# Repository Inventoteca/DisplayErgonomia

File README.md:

# DisplayErgonomia
Display que muestra diferentes valores del entorno. Usa NeoDígitos y varios sensores.  

+ Una Raspberry Pi Zero W controla los Neodígitos y recibe información de los sensores  
+ Almacena los valores que se podrían mostrar en forma de gráficas  
+ Los sensores de luz se instalan en la parte de arriba, cubiertos con una ventana de acrílico  
+ Caja para proteger raspberry y conexiones  
+ "Espiroqueta" para agrupar los cables  
+ Clema molex en los grupos de NeoDígitos para facilitar las conexiones  
+ NeoDígitos atornillados a base de MDF  
+ Raspberry con shield  

## Dígitos
Ocupa 17 NeoDígitos medianos que tienen 2 Neopixels por segmento más 2 Neopixels separados  
Son 16 Neopixels por dígito. En total son 272 Neopixels en el display  

La guía de Adafruit recomienda considerar que cada Neopixel consume 20 mA  
20 mA * 272 = 5.44 A
La Raspberry Zero W puede consumir 2 A  
5.44 A + 2 A = 7.44 A
Una fuente de 10 A es la elegida  

Cada Neopixel consume alrededor de 60 mA con brillo al máximo. 60 mA * 272 = 16.32 A  
Es muy raro que se lleguen a prender con el brillo máximo    
https://learn.adafruit.com/adafruit-neopixel-uberguide/individual-neopixels  

## Sensores

### ADC
Opciones de Convertidores Analógico a Digital  

MCP3008 - 8 channels of analog input with 10-bit precision  
ADS1x15 series - 4 channels with 12 to 16-bit precision and a programmable gain stage  
PCF8591 - 4 canales ADC, 1 canal DAC, resolución 8 bits, interfaz I2C  

https://learn.adafruit.com/raspberry-pi-analog-to-digital-converters  
https://articulo.mercadolibre.com.mx/MLM-544163593-modulo-analogico-digital-3-adc-1-dac-pcf8591-arduino-pic-dsp-_JM  

Se usa el **ADS1115** que tiene resolución de 16 bits.  

Datasheet  
https://www.ti.com/lit/ds/symlink/ads1113.pdf?ts=1616968419755  

Producto de Adafruit  
https://www.adafruit.com/product/1085  
https://github.com/adafruit/Adafruit_ADS1X15  

Tutorial para usar con Arduino  
https://www.luisllamas.es/entrada-analogica-adc-de-16-bits-con-arduino-y-ads1115/  

### Índice UV

Encontramos dos opciones para medir la radiación UV: Si1145 y ML8511.  
Se eligió el ML8511 porque la salida es voltaje analógico (no se requiere una librería específica para el sensor)
y tiene un fotodiodo sensible a la luz UV, en cambio el Si1145 no mide la luz UV directamente, la calcula
a partir de la luz visible e infrarroja.  

ML8511  
https://cdn.sparkfun.com/datasheets/Sensors/LightImaging/ML8511_3-8-13.pdf  
The ML8511 is a UV sensor, which is suitable for acquiring UV intensity indoors or outdoors. The ML8511 is
equipped with an internal amplifier, which converts photo-current to voltage depending on the UV intensity.
This unique feature offers an easy interface to external circuits such as ADC.  
Photodiode sensitive to UV-A and UV-B  
Analog voltage output  
Operating Voltage 3.3 V  
Output Voltage 1.0 - 3.0 V (depende de temperatura)  
Se debe conectar ADC a la salida  
280 a 390nm  

Si1145  
https://learn.adafruit.com/adafruit-si1145-breakout-board-uv-ir-visible-sensor  
https://github.com/adafruit/Adafruit-Si1145-Light-Sensor-PCB  
https://cdn-shop.adafruit.com/datasheets/Si1145-46-47.pdf  
The SI1145 (from SiLabs) has a calibrated UV sensing algorithm that can calculate UV Index.
It doesn't contain an actual UV sensing element, instead it approximates it based on visible & IR light from the sun.
Works over I2C so just about any microcontroller can use it.
Has individual visible and IR sensing elements, but the library doesn't calculate the exact values of IR and Visible light.
If you need precision Lux measurement check out the TSL2561.

### Sonido
Probaremos con el módulo KY-037 tomando muestras con el ADS1115.  

Tutorial para usar con Arduino  
https://create.arduino.cc/projecthub/electropeak/how-to-use-ky-037-sound-detection-sensor-with-arduino-a757a7  

Otras opciones para medir sonido se muestran abajo. No se han probado.  

Hat con micrófono  
https://medium.com/homeday/building-a-noise-level-dashboard-for-your-office-with-a-raspberry-pi-71360ee1ff46  
https://thepihut.com/products/respeaker-4-mic-array-for-raspberry-pi  

¿Usar la entrada de micrófono o un micrófono USB?  
https://www.raspberrypi.org/forums/viewtopic.php?t=258965  

Diseño de una herramienta de medición de ruidos (con módulo micrófono DfRobot 0034)  
http://www.scielo.org.co/pdf/pml/v12n1/1909-0455-pml-12-01-00081.pdf  

### Luz (emitancia luminosa)  
Se mide en lux  
https://es.wikipedia.org/wiki/Emitancia_luminosa  

El sensor elegido es el **TSL2561**. Es fácil de usar con las librerías.  
El valor en el display se podría mostrar en kilolux, de ese modo se puede mostrar todo el rango
de medición del sensor 0.001 hasta 40.00 kilolux.  

Tutoriales (Arduino)  
https://learn.adafruit.com/tsl2561/overview  
https://hetpro-store.com/TUTORIALES/sensor-de-luz-tsl2560/  

Datasheet  
https://ams.com/TSL2561#tab/documents  

### Calidad del aire
El sensor MQ-135 se utiliza en equipos de control de calidad del aire para edificios y oficinas,
son adecuados para la detección de NH3, NOx, alcohol, benceno, humo, CO2, etc.  
Se debe calibrar.  

Tutoriales para empezar con Arduino  
https://naylampmechatronics.com/blog/42_tutorial-sensores-de-gas-mq2-mq3-mq7-y-mq135.html  
https://www.luisllamas.es/arduino-detector-gas-mq/  

Datasheet  
http://www.china-total.com/Product/meter/gas-sensor/MQ135.pdf  
http://www.china-total.com/Product/meter/gas-sensor/Gas-sensor.htm  

Librería para sensores MQ  
Podemos basarnos en las funciones de regresión  
https://github.com/miguel5612/MQSensorsLib  

## Raspberry
Los sensores serán leidos por la Raspberry y sus valores serán mostrados por los NeoDígitos, el programa funciona con Node-RED, con 
los módulos necesarios y librerias contenidas en una imagen de Docker. El control de los Dígitos está realizado por un nodo desarrollado 
por nosotros. Otro contenedor de Docker administrará el WiFi, para ser el medio de configuración del panel, através de un Dashboard.

Wifi  
Es necesario configurar la Raspberry como AP + Client al mismo tiempo, se realizó con las instrucciones siguientes, basadas en este tutorial.  
https://pifi.imti.co/  

- Con la Raspberry corriendo ya algún S.O. y conectada a Internet por cable, con SSH activado, 
se procede a desconecatar el wifi del sistema y se le pasa el control a un contenedor de Docker.
- Se ha probado con RPi Zero W, RPi 3. Se debe terminar la configuración de país del wifi antes de proceder a quitarlo del sistema.

## Diagramas
Dibujos de conexiones se encuentran en la carpeta `Diagramas`.

## Diseños
La carpeta `Diseños` contiene 

+ El modelo 3D del display
+ Piezas en STL para imprimir
+ Los dibujos para cortar las piezas de MDF
+ PCBs en formato Eagle

## Documentos
En la carpeta `Documentos` está la hoja de cotización y otra información privada.

## Fotos
En la carpeta `Fotos` hay imágenes del proceso de ensamblaje.

## Programa
La carpeta `Programa` contiene 

+ Descripciones de las librerías
+ Comandos utilizados para instalar las librerías
+ Capturas de pantalla

Se ha creado un repositorio independiente para sincronizar los programas desde Node-RED.
Contiene los flujos de Node-RED y programas escritos en python.  
https://github.com/Inventoteca/DisplayErgonomiaFlows

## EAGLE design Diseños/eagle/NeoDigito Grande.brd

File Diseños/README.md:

En esta carpeta se encuentran los diseños las piezas para armar el
Display Ergonomía.

En primer lugar está el ensamblaje completo en formato step.

En la carpeta `corte_laser` se tienen los dibujos para cortar mdf de 3 mm y 6 mm. 
El archivo `Panel ergonomia corte.dwg` es el primer diseño que enviaron para 
cortar el panel frontal. Se redibujó y se agregaron los puntos decimales de 
los dígitos y perforaciones para las pijas.  

En la carpeta `eagle` se tienen estos diseños
- Tres tamaños de NeoDigitos
- Shield para Raspberry Pi Zero
- Placas para los sensores
- Placas para las borneras

En el display se utilizan los NeoDigitos medianos V2 y el shield para Rasp.

La carpeta `stl` contiene modelos para fabricar con impresión 3D. Son cajas
para los sensores y separadores para las placas de las borneras.

----

## Modelos 3D descargados  

Caja 25 x 15 x 10 cm  
https://grabcad.com/library/lemotech-ip67-junction-box-250-mm-x-150-mm-x-100-mm-1  

Otras cajas (no descargadas)  
https://grabcad.com/library/ip65-ip67-electrical-enclosures-2/details?folder_id=4320709  

Power supply 12V 20A by T-Maker  
https://grabcad.com/library/power-supply-12v-20a-by-t-maker-1/details?folder_id=9293058  
Editada para acercarse a las medidas de la fuente comprada  

ADS1115  
https://grabcad.com/library/16bit-i2c-adc-pga-ads1115-1  

TSL2561  
https://grabcad.com/library/tsl2561-breakout-board-1  

Sensores MQ  
https://grabcad.com/library/mq-2-gas-sensor-1  
https://grabcad.com/library/mq3-sensor-1  
https://grabcad.com/library/mq135-air-sensor-1  
https://grabcad.com/library/mq2-gas-sensor-1  

DHT22  
https://grabcad.com/library/dht22-am2302-1  

Sensor de sonido (micrófono)  
https://grabcad.com/library/microphone-sound-detection-sensor-module-1  

Colección de conectores JST y headers Dupont  
https://grabcad.com/library/jst-eh-2-5mm-connector-pack-1  
https://grabcad.com/library/female-header-pitch-2-54mm-straight-single-row-2-to-40-1

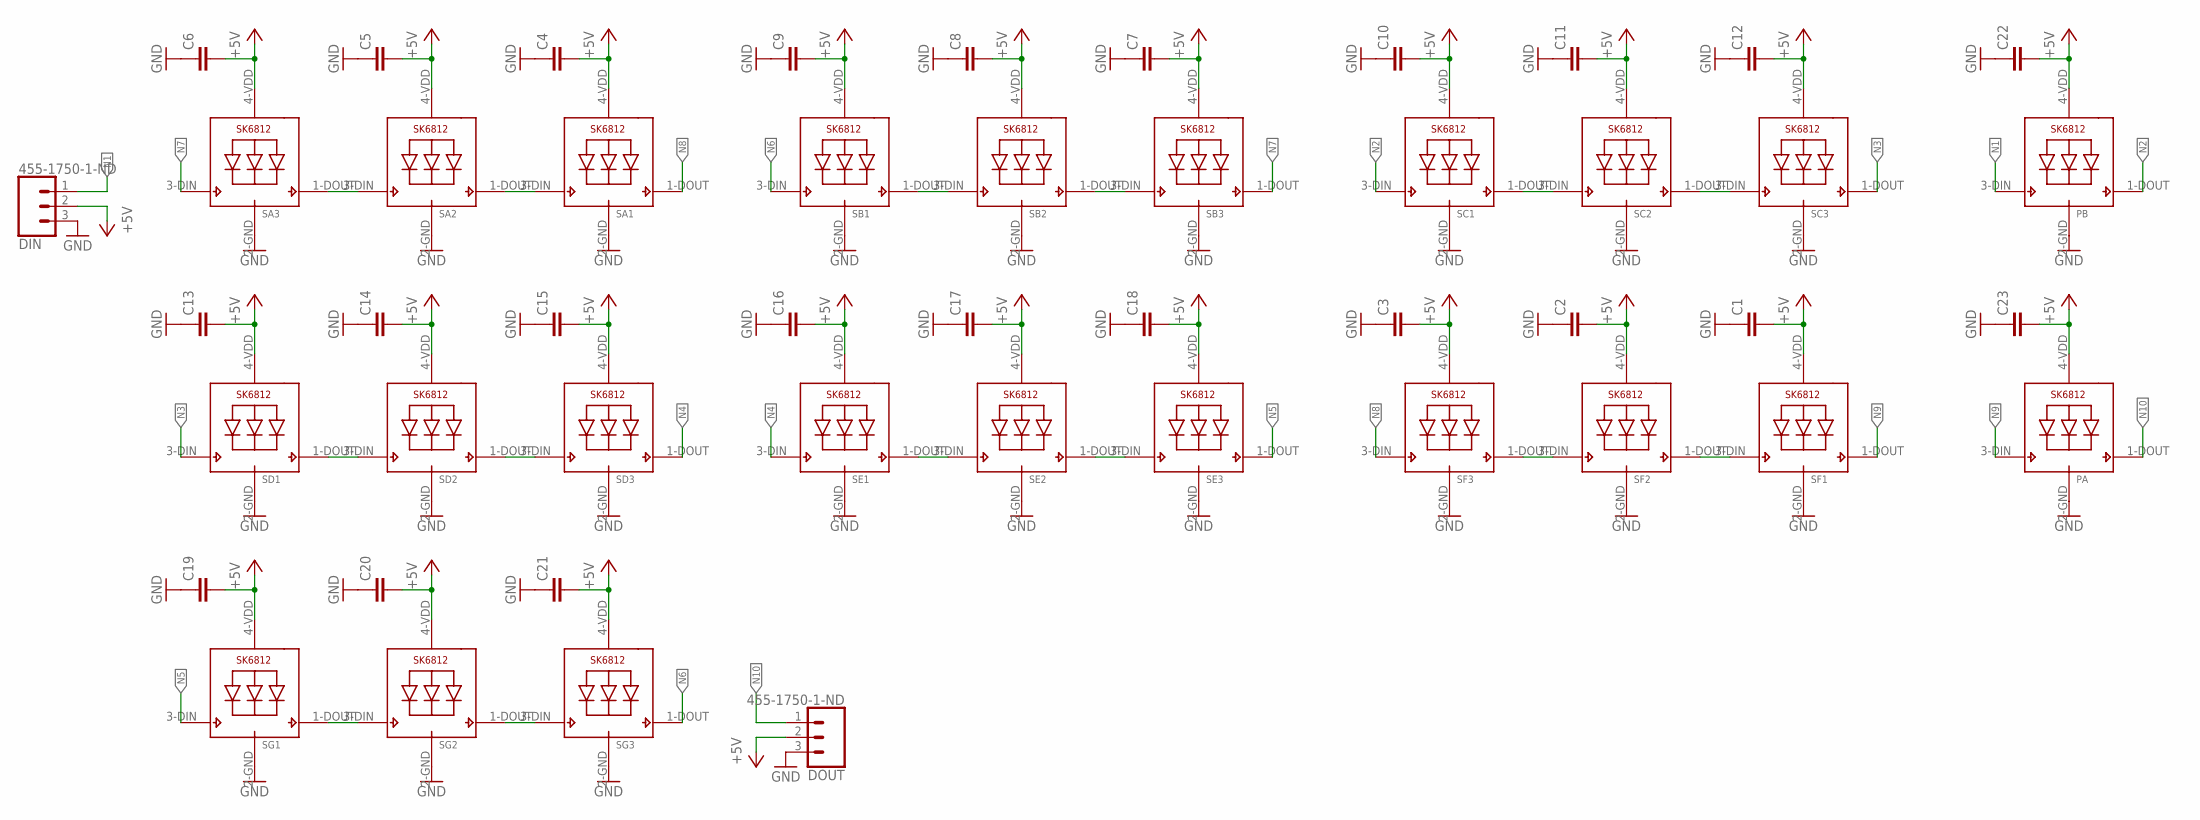
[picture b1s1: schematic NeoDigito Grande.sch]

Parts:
C1, C2, C3, C4, C5, C6, C7, C8, C9, C10, C11, C12, C13, C14, C15, C16, C17, C18, C19, C20, C21, C22, C23: C-EUC0805; C0805
DIN: 455-1750-1-ND; 1X03
DOUT: 455-1750-1-ND; 1X03_NO_SILK
PA: SK6812_3535; LED3535
PB: SK6812_3535; LED3535
SA1, SA2, SA3: SK6812_3535; LED3535
SB1, SB2, SB3: SK6812_3535; LED3535
SC1, SC2, SC3: SK6812_3535; LED3535
SD1, SD2, SD3: SK6812_3535; LED3535
SE1, SE2, SE3: SK6812_3535; LED3535
SF1, SF2, SF3: SK6812_3535; LED3535
SG1, SG2, SG3: SK6812_3535; LED3535

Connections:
+5V: C1.2, C2.2, C3.2, C4.2, C5.2, C6.2, C7.2, C8.2, C9.2, C10.2, C11.2, C12.2, C13.2, C14.2, C15.2, C16.2, C17.2, C18.2, C19.2, C20.2, C21.2, C22.2, C23.2, DIN.2, DOUT.2, PA.4-VDD (VDD), PB.4-VDD (VDD), SA1.4-VDD (VDD), SA2.4-VDD (VDD), SA3.4-VDD (VDD), SB1.4-VDD (VDD), SB2.4-VDD (VDD), SB3.4-VDD (VDD), SC1.4-VDD (VDD), SC2.4-VDD (VDD), SC3.4-VDD (VDD), SD1.4-VDD (VDD), SD2.4-VDD (VDD), SD3.4-VDD (VDD), SE1.4-VDD (VDD), SE2.4-VDD (VDD), SE3.4-VDD (VDD), SF1.4-VDD (VDD), SF2.4-VDD (VDD), SF3.4-VDD (VDD), SG1.4-VDD (VDD), SG2.4-VDD (VDD), SG3.4-VDD (VDD)
GND: C1.1, C2.1, C3.1, C4.1, C5.1, C6.1, C7.1, C8.1, C9.1, C10.1, C11.1, C12.1, C13.1, C14.1, C15.1, C16.1, C17.1, C18.1, C19.1, C20.1, C21.1, C22.1, C23.1, DIN.3, DOUT.3, PA.2-GND (GND), PB.2-GND (GND), SA1.2-GND (GND), SA2.2-GND (GND), SA3.2-GND (GND), SB1.2-GND (GND), SB2.2-GND (GND), SB3.2-GND (GND), SC1.2-GND (GND), SC2.2-GND (GND), SC3.2-GND (GND), SD1.2-GND (GND), SD2.2-GND (GND), SD3.2-GND (GND), SE1.2-GND (GND), SE2.2-GND (GND), SE3.2-GND (GND), SF1.2-GND (GND), SF2.2-GND (GND), SF3.2-GND (GND), SG1.2-GND (GND), SG2.2-GND (GND), SG3.2-GND (GND)
N1: DIN.1, PB.3-DIN (DI)
N2: PB.1-DOUT (DO), SC1.3-DIN (DI)
N3: SC3.1-DOUT (DO), SD1.3-DIN (DI)
N4: SD3.1-DOUT (DO), SE1.3-DIN (DI)
N5: SE3.1-DOUT (DO), SG1.3-DIN (DI)
N6: SB1.3-DIN (DI), SG3.1-DOUT (DO)
N7: SA3.3-DIN (DI), SB3.1-DOUT (DO)
N8: SA1.1-DOUT (DO), SF3.3-DIN (DI)
N9: PA.3-DIN (DI), SF1.1-DOUT (DO)
N10: DOUT.1, PA.1-DOUT (DO)
unnamed: SA2.3-DIN (DI), SA3.1-DOUT (DO)
unnamed: SA1.3-DIN (DI), SA2.1-DOUT (DO)
unnamed: SB1.1-DOUT (DO), SB2.3-DIN (DI)
unnamed: SB2.1-DOUT (DO), SB3.3-DIN (DI)
unnamed: SC1.1-DOUT (DO), SC2.3-DIN (DI)
unnamed: SC2.1-DOUT (DO), SC3.3-DIN (DI)
unnamed: SD1.1-DOUT (DO), SD2.3-DIN (DI)
unnamed: SD2.1-DOUT (DO), SD3.3-DIN (DI)
unnamed: SG1.1-DOUT (DO), SG2.3-DIN (DI)
unnamed: SG2.1-DOUT (DO), SG3.3-DIN (DI)
unnamed: SE1.1-DOUT (DO), SE2.3-DIN (DI)
unnamed: SE2.1-DOUT (DO), SE3.3-DIN (DI)
unnamed: SF2.3-DIN (DI), SF3.1-DOUT (DO)
unnamed: SF1.3-DIN (DI), SF2.1-DOUT (DO)

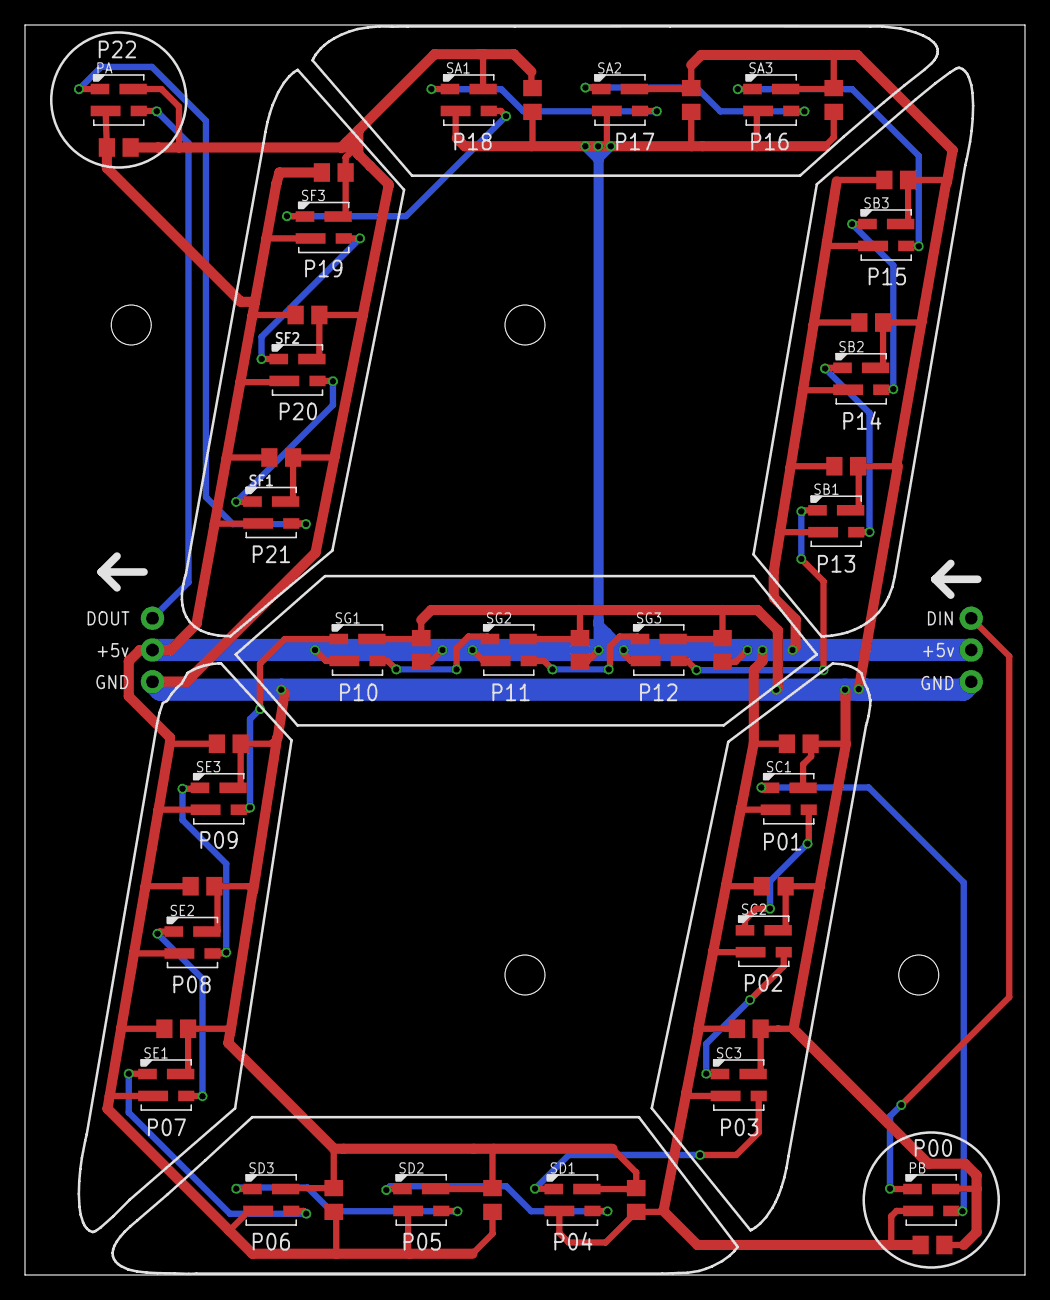
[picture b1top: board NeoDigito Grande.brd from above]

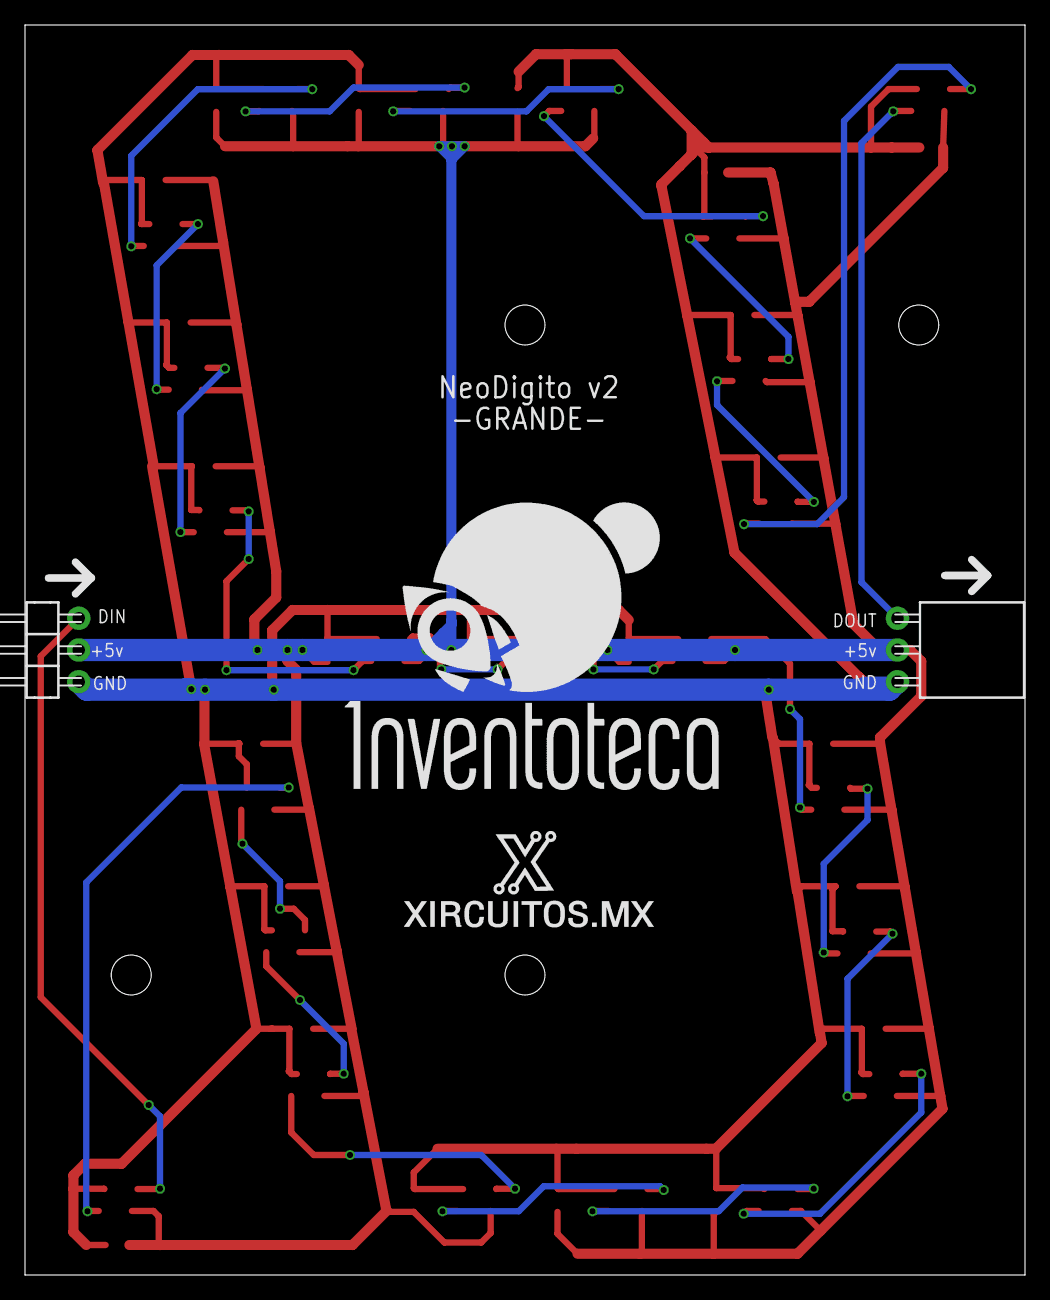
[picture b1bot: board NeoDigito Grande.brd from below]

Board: 2 copper layers, 80.0 x 100.0 mm, 48 parts (2 on the bottom side), 26 nets.

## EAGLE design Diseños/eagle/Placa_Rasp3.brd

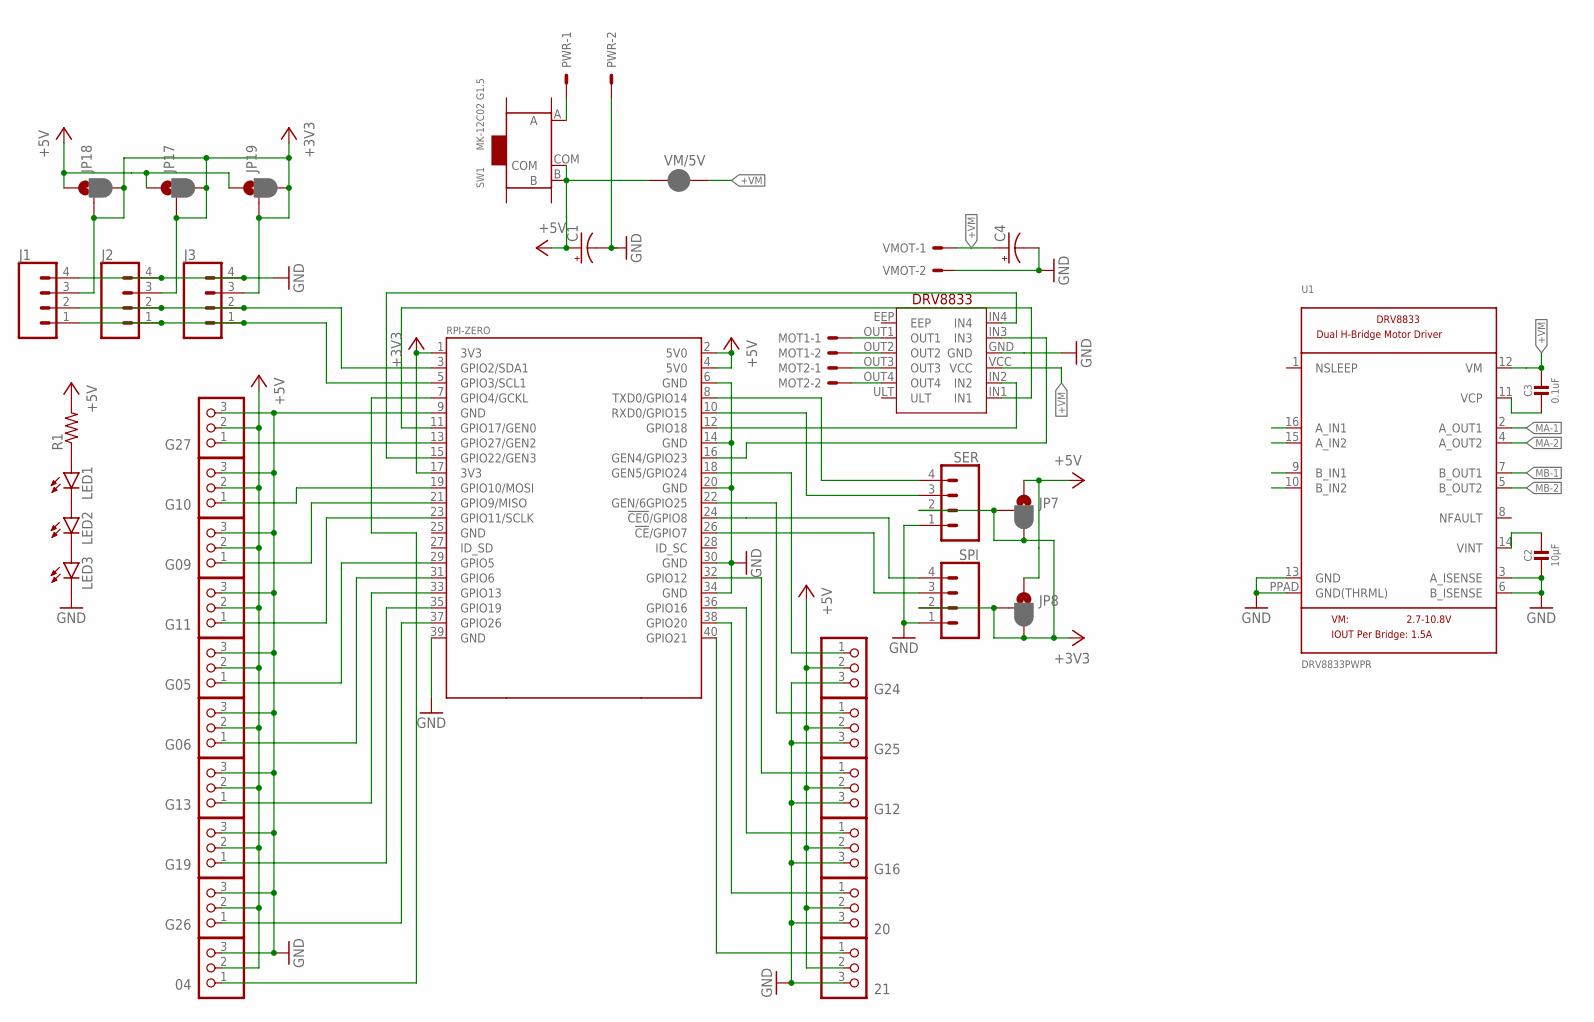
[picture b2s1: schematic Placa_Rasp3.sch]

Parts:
04, 20, 21: PINHD-1X3; 1X03
C1, C4: CPOL-USE2,5-6E; E2,5-6E
C2: 10µF; 0805-NO
C3: 0.1uF; 0805-NO
G05, G06, G09, G10, G11, G12, G13, G16, G19, G24, G25, G26, G27: PINHD-1X3; 1X03
J1, J2, J3: CONN_04; 1X04
JP7, JP8, JP17, JP18, JP19: JUMPER-SMT_3_1-NC_PASTE_SILK; SMT-JUMPER_3_1-NC_PASTE_SILK
LED1, LED2, LED3: LEDCHIP-LED0603; CHIP-LED0603
MOT1, MOT2: JST-XH-02-PIN-LONG-PAD; JST-XH-02-PACKAGE-LONG-PAD
PWR: JST-XH-02-PIN-LONG-PAD; JST-XH-02-PACKAGE-LONG-PAD
R1: R-US_R0603; R0603
SER: CONN_04; 1X04
SPI: CONN_04; 1X04
SW1: MK-12C02 G1.5; SW7-SMD-L6.7X2.7X3.2MM
U1: DRV8833PWPR; HTSSOP16
U$1: RPI-ZERO; RASPBERRYPI_BASTELSTUBE_V13_RASPI_BOARD_B+_FULL
U$3: DVR8833; DRV8833
VM/5V: JUMPER-SMT_2_NC_PASTE_SILK; SMT-JUMPER_2_NC_PASTE_SILK
VMOT: JST-XH-02-PIN-LONG-PAD; JST-XH-02-PACKAGE-LONG-PAD

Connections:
+3V3: J1.3, J2.3, J3.3, JP7.2, JP7.3, JP8.2, JP8.3, JP17.2, JP17.3, JP18.2, JP18.3, JP19.2, JP19.3, SER.2, SPI.2, U$1.1 (3V3), U$1.17 (3V3)
+5V: 04.2, 20.2, 21.2, C1.+, G05.2, G06.2, G09.2, G10.2, G11.2, G12.2, G13.2, G16.2, G19.2, G24.2, G25.2, G26.2, G27.2, JP7.1, JP8.1, JP17.1, JP18.1, JP19.1, R1.2, SW1.B, SW1.COM, U$1.2 (5V0), U$1.4 (5V0), VM/5V.1
+VM: C3.1, C4.+, U1.12 (VM), U$3.VCC, VM/5V.2, VMOT.1
CS0: SPI.4, U$1.24 (!CE0!/GPIO8)
CS1: SPI.3, U$1.26 (!CE!/GPIO7)
G17: U$1.11 (GPIO17/GEN0), U$3.IN1
G18: U$1.12 (GPIO18), U$3.IN2
G22: U$1.15 (GPIO22/GEN3), U$3.IN4
G23: U$1.16 (GEN4/GPIO23), U$3.IN3
GND: 04.3, 20.3, 21.3, C1.-, C2.1, C4.-, G05.3, G06.3, G09.3, G10.3, G11.3, G12.3, G13.3, G16.3, G19.3, G24.3, G25.3, G26.3, G27.3, J1.4, J2.4, J3.4, LED3.C, PWR.2, SER.1, SPI.1, U1.3 (A_ISENSE), U1.6 (B_ISENSE), U1.13 (GND), U1.PPAD (GND(THRML)), U$1.6 (GND), U$1.9 (GND), U$1.14 (GND), U$1.20 (GND), U$1.30 (GND), U$1.34 (GND), U$1.39 (GND), U$3.GND, VMOT.2
MA-1: MOT1.1, U1.2 (A_OUT1), U$3.OUT1
MA-2: MOT1.2, U1.4 (A_OUT2), U$3.OUT2
MB-1: MOT2.2, U1.7 (B_OUT1), U$3.OUT4
MB-2: MOT2.1, U1.5 (B_OUT2), U$3.OUT3
unnamed: G26.1, U$1.37 (GPIO26)
unnamed: G24.1, U$1.18 (GEN5/GPIO24)
unnamed: G25.1, U$1.22 (GEN/6GPIO25)
unnamed: G12.1, U$1.32 (GPIO12)
unnamed: G16.1, U$1.36 (GPIO16)
unnamed: PWR.1, SW1.A
unnamed: 20.1, U$1.38 (GPIO20)
unnamed: 21.1, U$1.40 (GPIO21)
unnamed: LED1.C, LED2.A
unnamed: LED2.C, LED3.A
unnamed: LED1.A, R1.1
unnamed: G27.1, U$1.13 (GPIO27/GEN2)
unnamed: G10.1, U$1.19 (GPIO10/MOSI)
unnamed: G11.1, U$1.23 (GPIO11/SCLK)
unnamed: G09.1, U$1.21 (GPIO9/MISO)
unnamed: G05.1, U$1.29 (GPIO5)
unnamed: G06.1, U$1.31 (GPIO6)
unnamed: G13.1, U$1.33 (GPIO13)
unnamed: G19.1, U$1.35 (GPIO19)
unnamed: 04.1, U$1.7 (GPIO4/GCKL)
unnamed: C2.2, U1.14 (VINT)
unnamed: C3.2, U1.11 (VCP)
RX: SER.3, U$1.10 (RXD0/GPIO15)
SCL: J1.1, J2.1, J3.1, U$1.5 (GPIO3/SCL1)
SDA: J1.2, J2.2, J3.2, U$1.3 (GPIO2/SDA1)
TX: SER.4, U$1.8 (TXD0/GPIO14)

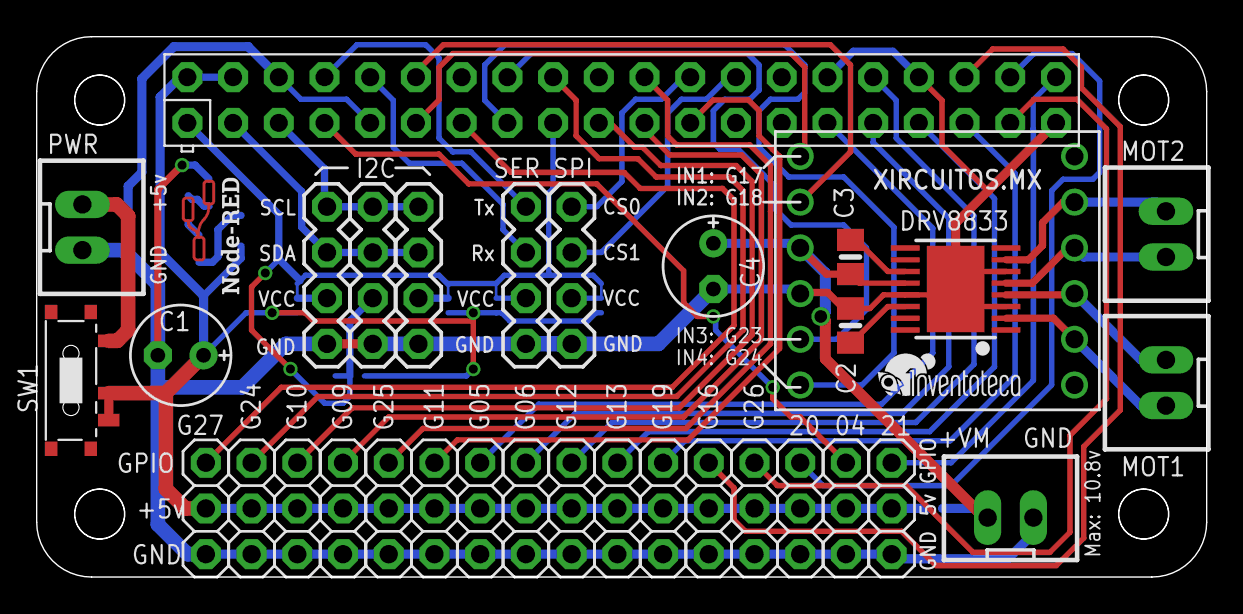
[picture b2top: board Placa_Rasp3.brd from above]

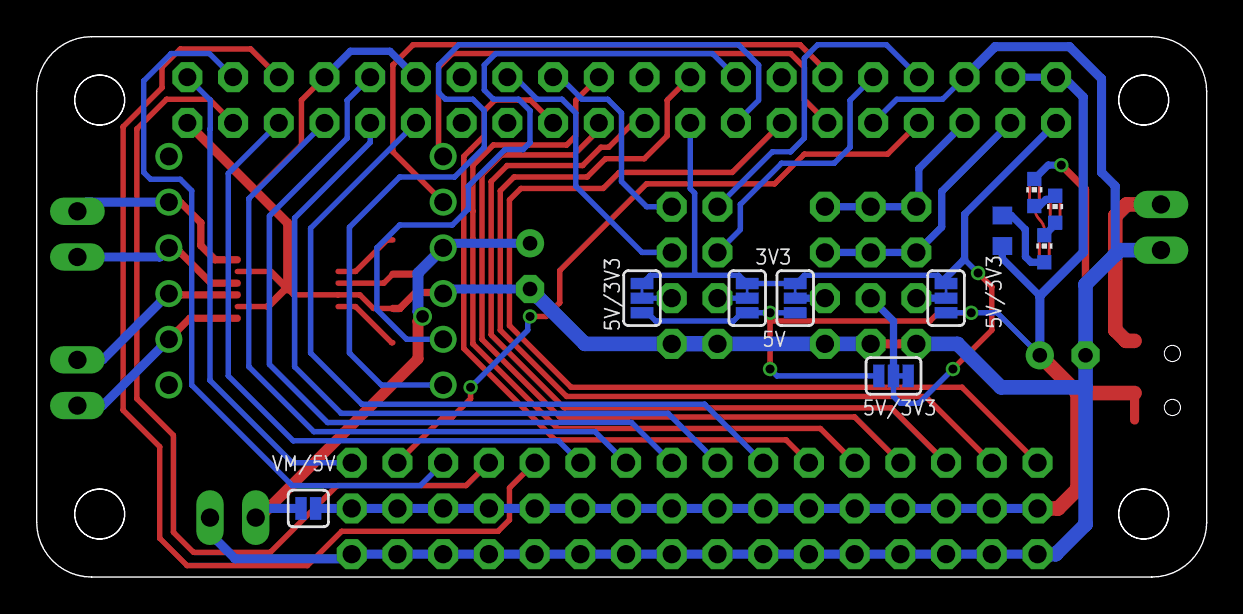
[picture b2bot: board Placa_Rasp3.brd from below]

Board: 2 copper layers, 65.0 x 30.0 mm, 43 parts (10 on the bottom side), 40 nets.

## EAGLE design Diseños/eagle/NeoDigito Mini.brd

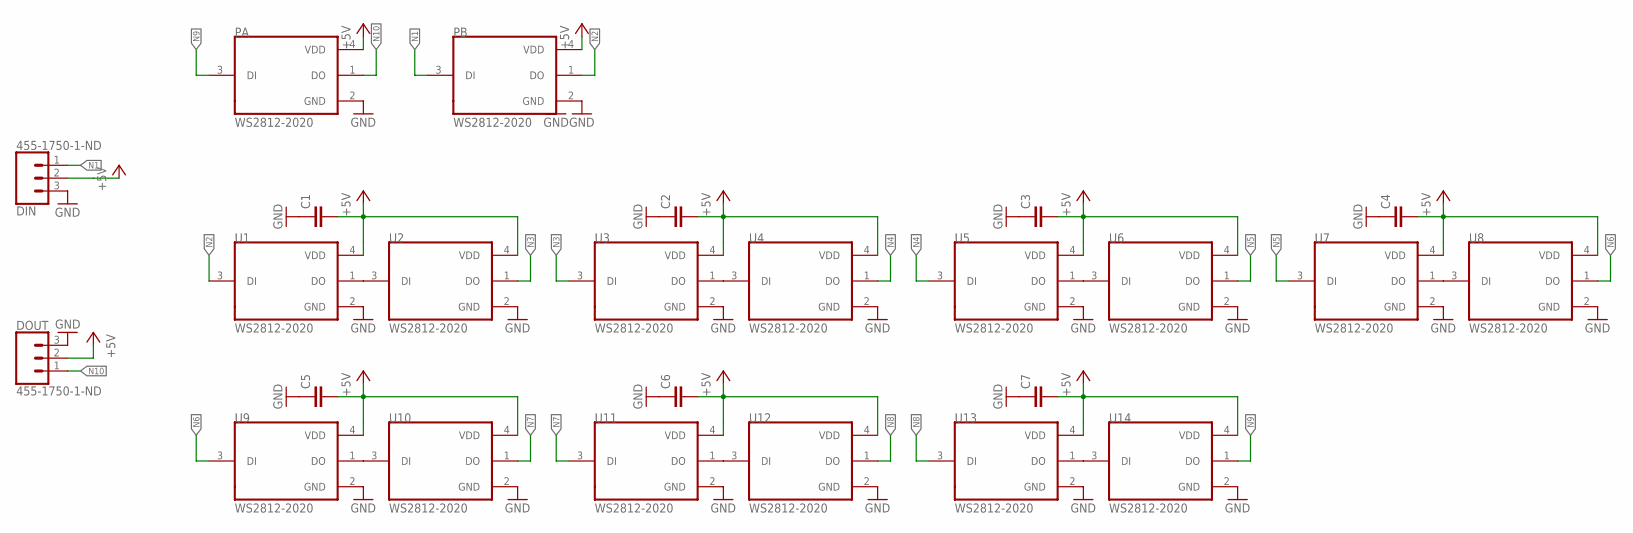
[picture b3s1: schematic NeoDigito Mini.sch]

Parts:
C1, C2, C3, C4, C5, C6, C7: C-EUC0805; C0805
DIN: 455-1750-1-ND; 1X03
DOUT: 455-1750-1-ND; 1X03
PA: WS2812-2020; LED_WS2812-2020
PB: WS2812-2020; LED_WS2812-2020
U1, U2, U3, U4, U5, U6, U7, U8, U9, U10, U11, U12, U13, U14: WS2812-2020; LED_WS2812-2020

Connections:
+5V: C1.2, C2.2, C3.2, C4.2, C5.2, C6.2, C7.2, DIN.2, DOUT.2, PA.4 (VDD), PB.4 (VDD), U1.4 (VDD), U2.4 (VDD), U3.4 (VDD), U4.4 (VDD), U5.4 (VDD), U6.4 (VDD), U7.4 (VDD), U8.4 (VDD), U9.4 (VDD), U10.4 (VDD), U11.4 (VDD), U12.4 (VDD), U13.4 (VDD), U14.4 (VDD)
GND: C1.1, C2.1, C3.1, C4.1, C5.1, C6.1, C7.1, DIN.3, DOUT.3, PA.2 (GND), PB.2 (GND), U1.2 (GND), U2.2 (GND), U3.2 (GND), U4.2 (GND), U5.2 (GND), U6.2 (GND), U7.2 (GND), U8.2 (GND), U9.2 (GND), U10.2 (GND), U11.2 (GND), U12.2 (GND), U13.2 (GND), U14.2 (GND)
N1: DIN.1, PB.3 (DI)
N2: PB.1 (DO), U1.3 (DI)
N3: U2.1 (DO), U3.3 (DI)
N4: U4.1 (DO), U5.3 (DI)
N5: U6.1 (DO), U7.3 (DI)
N6: U8.1 (DO), U9.3 (DI)
N7: U10.1 (DO), U11.3 (DI)
N8: U12.1 (DO), U13.3 (DI)
N9: PA.3 (DI), U14.1 (DO)
N10: DOUT.1, PA.1 (DO)
unnamed: U1.1 (DO), U2.3 (DI)
unnamed: U3.1 (DO), U4.3 (DI)
unnamed: U5.1 (DO), U6.3 (DI)
unnamed: U7.1 (DO), U8.3 (DI)
unnamed: U9.1 (DO), U10.3 (DI)
unnamed: U11.1 (DO), U12.3 (DI)
unnamed: U13.1 (DO), U14.3 (DI)

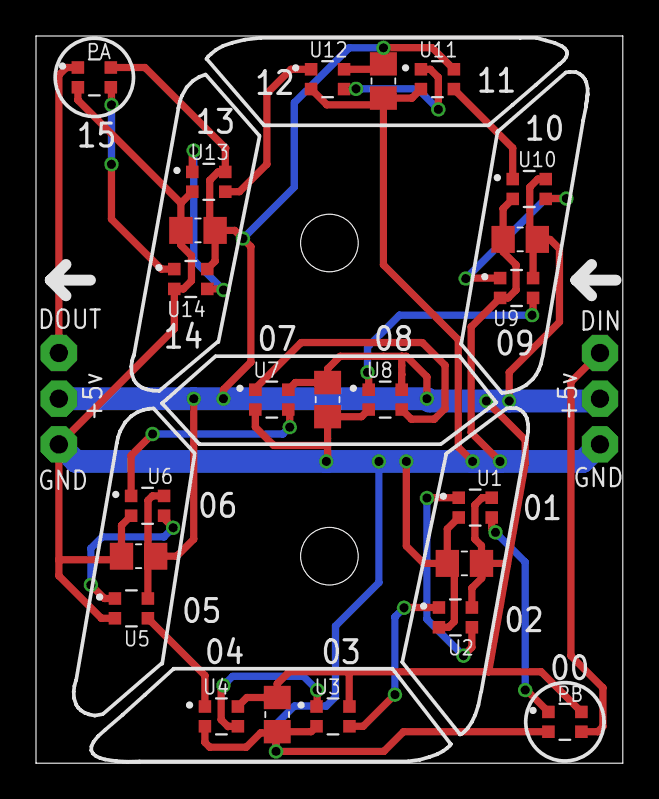
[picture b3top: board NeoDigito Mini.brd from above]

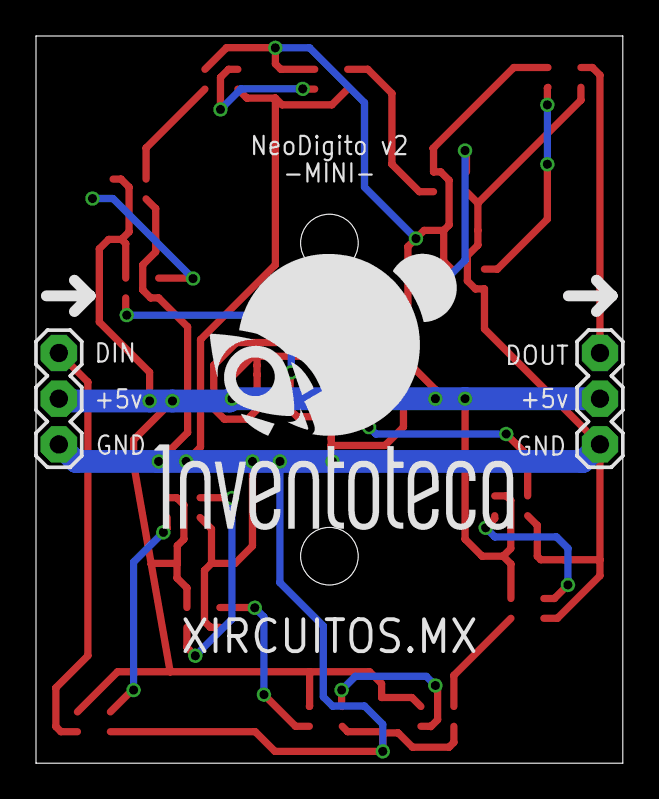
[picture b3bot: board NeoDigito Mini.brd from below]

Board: 2 copper layers, 32.6 x 40.4 mm, 25 parts (2 on the bottom side), 19 nets.

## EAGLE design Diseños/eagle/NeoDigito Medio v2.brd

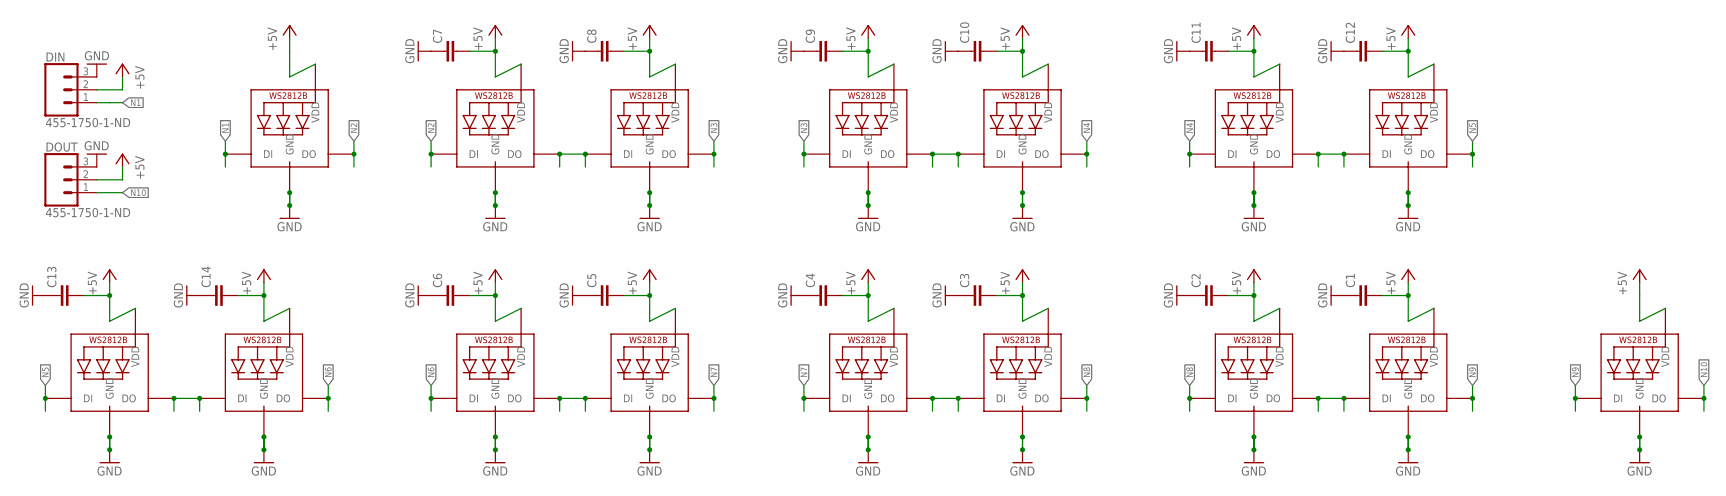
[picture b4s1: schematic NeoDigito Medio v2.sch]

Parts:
C1, C2, C3, C4, C5, C6, C7, C8, C9, C10, C11, C12, C13, C14: C-EUC0805; C0805
DIN: 455-1750-1-ND; 1X03
DOUT: 455-1750-1-ND; 1X03_NO_SILK
PA.: WS2812B3535; LED3535
PB.: WS2812B3535; LED3535
SA1., SA2.: WS2812B3535; LED3535
SB1., SB2.: WS2812B3535; LED3535
SC1., SC2.: WS2812B3535; LED3535
SD1., SD2.: WS2812B3535; LED3535
SE1., SE2.: WS2812B3535; LED3535
SF1., SF2.: WS2812B3535; LED3535
SG1., SG2.: WS2812B3535; LED3535

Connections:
+5V: C1.2, C2.2, C3.2, C4.2, C5.2, C6.2, C7.2, C8.2, C9.2, C10.2, C11.2, C12.2, C13.2, C14.2, DIN.2, DOUT.2, PA..2 (VDD), PB..2 (VDD), SA1..2 (VDD), SA2..2 (VDD), SB1..2 (VDD), SB2..2 (VDD), SC1..2 (VDD), SC2..2 (VDD), SD1..2 (VDD), SD2..2 (VDD), SE1..2 (VDD), SE2..2 (VDD), SF1..2 (VDD), SF2..2 (VDD), SG1..2 (VDD), SG2..2 (VDD)
GND: C1.1, C2.1, C3.1, C4.1, C5.1, C6.1, C7.1, C8.1, C9.1, C10.1, C11.1, C12.1, C13.1, C14.1, DIN.3, DOUT.3, PA..4 (GND), PB..4 (GND), SA1..4 (GND), SA2..4 (GND), SB1..4 (GND), SB2..4 (GND), SC1..4 (GND), SC2..4 (GND), SD1..4 (GND), SD2..4 (GND), SE1..4 (GND), SE2..4 (GND), SF1..4 (GND), SF2..4 (GND), SG1..4 (GND), SG2..4 (GND)
N1: DIN.1, PB..1 (DI)
N2: PB..3 (DO), SC1..1 (DI)
N3: SC2..3 (DO), SD1..1 (DI)
N4: SD2..3 (DO), SE1..1 (DI)
N5: SE2..3 (DO), SG1..1 (DI)
N6: SB1..1 (DI), SG2..3 (DO)
N7: SA1..1 (DI), SB2..3 (DO)
N8: SA2..3 (DO), SF1..1 (DI)
N9: PA..1 (DI), SF2..3 (DO)
N10: DOUT.1, PA..3 (DO)
unnamed: SE1..3 (DO), SE2..1 (DI)
unnamed: SC1..3 (DO), SC2..1 (DI)
unnamed: SA1..3 (DO), SA2..1 (DI)
unnamed: SF1..3 (DO), SF2..1 (DI)
unnamed: SD1..3 (DO), SD2..1 (DI)
unnamed: SG1..3 (DO), SG2..1 (DI)
unnamed: SB1..3 (DO), SB2..1 (DI)

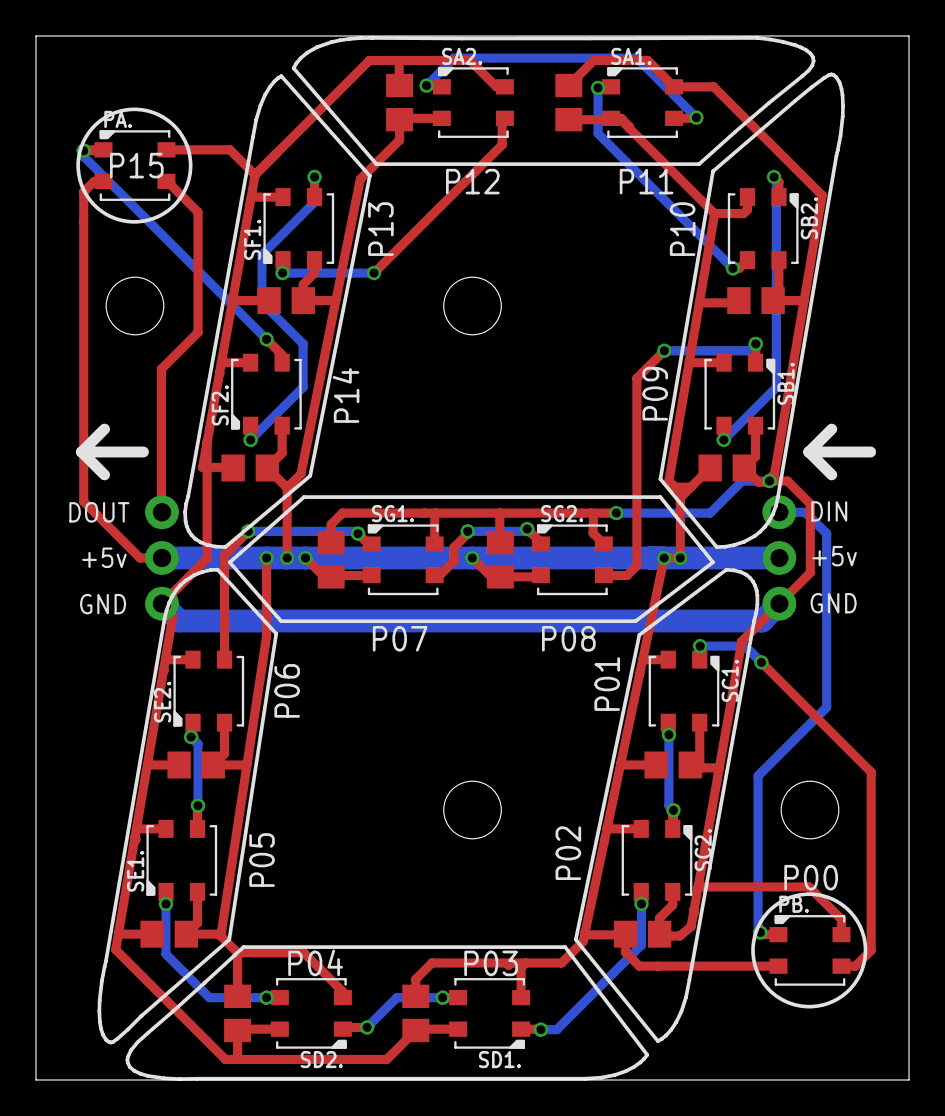
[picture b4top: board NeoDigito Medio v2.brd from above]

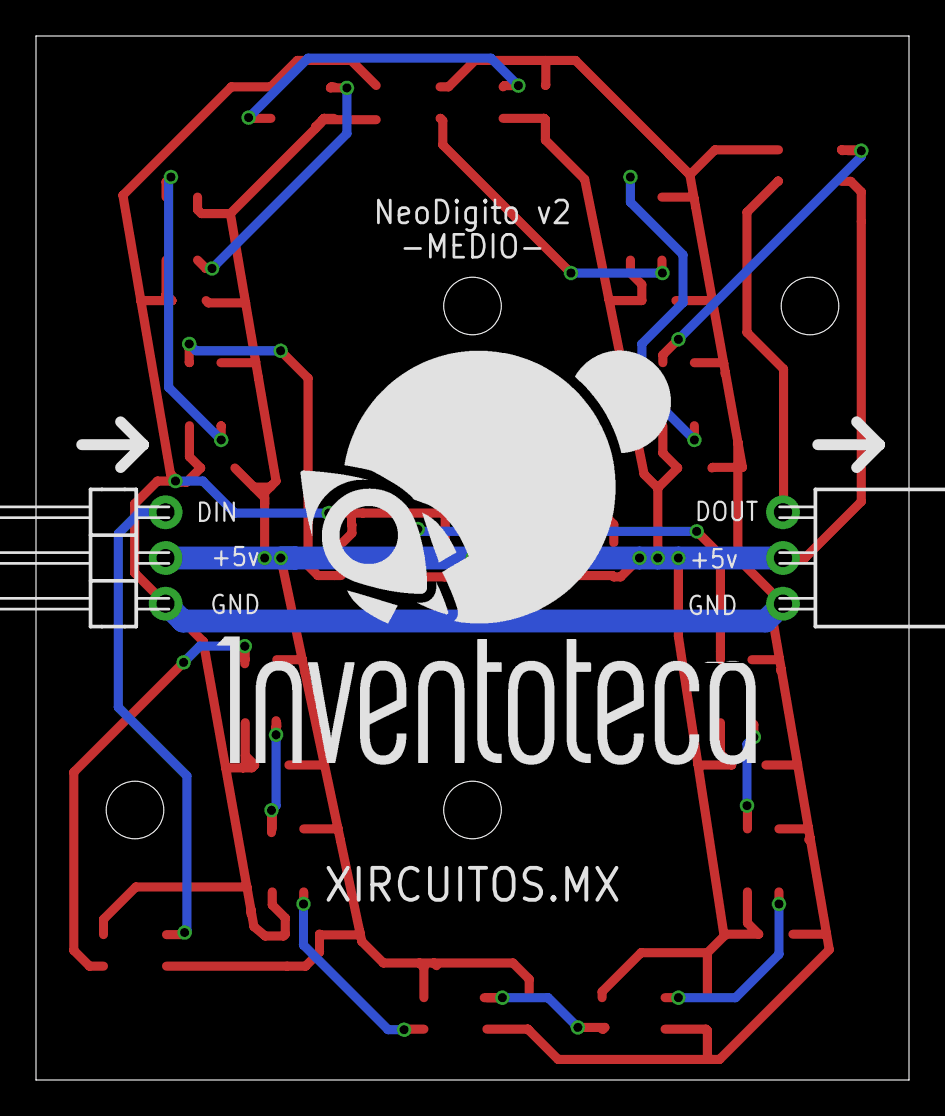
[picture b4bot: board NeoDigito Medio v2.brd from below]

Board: 2 copper layers, 48.5 x 58.0 mm, 32 parts (2 on the bottom side), 19 nets.

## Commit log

2021-03-12 resumen sensores UV
2021-03-12 Info ADCs
2021-03-12 Primeros archivos docs, fotos y diseños
2021-03-12 info sonido
2021-03-12 Link modelo 3D fuente
2021-03-15 Puntos importantes en diseño
2021-03-16 foto primera lista de materiales
2021-03-16 Enlaces modelos 3D de sensores
2021-03-19 Links modelos conectores
2021-03-30 Agregar info de sensores MQ, sonido y luz
2021-03-30 Borrar lista de modelos descargados
2021-03-30 Crear README, lista de modelos descargados
2021-03-30 Resumen de carpetas diseños y programa
2021-03-31 Capturas de pantalla
2021-03-31 info libs ADS1115
2021-03-31 Info DHT
2021-03-31 renombras capturas 1
2021-03-31 dibujos grupo 2 digitos
2021-03-31 dibujos grupos 3 y 4 digitos
2021-03-31 dibujos panel frontal
2021-04-12 fotos ensamblando mdf y pruebas con arduino
2021-04-12 capturas creando proyecto en node-red y repo vacío
2021-04-12 como usar exec con python y loop infinito
2021-04-12 link al repo de flows
2021-04-12 instrucciones librería DHT
2021-04-14 Info de lib para neopixels y ADS115 con python
2021-04-16 Info para calibrar sensor UV
2021-04-16 Poca info calibración sensor de sonido y aire
2021-04-16 ideas para medir decibeles
2021-05-07 fotos ensamblado
2021-05-19 Nota lib python tsl256
2021-05-19 Nota serializar json
2021-07-01 Organizar y subir archivos Eagle
2021-07-01 Descripción de categorías
2021-07-01 Subir diseños
2021-07-01 Subir diagrama general
2021-07-01 Actualizar readme
2022-09-12 Programa en Arduino para el panel
    Esta versión, será compatible con el App que se está desarrollando en flutter
2022-09-18 websocket ready
    Listo para intercambiar inforfación "json" a través de websocket y la app de ejemplo
2022-09-23 Json-RPC Ready
    Comunicación JsonRPC por Serial y WebSocket
2022-11-18 Noise sensor
    Documentation using new Serial-TTL Sensor for noise
2023-01-13 ESP32 Firmware
2023-01-25 neodigito
2023-01-28 esp testing
2023-01-29 pc tienda
2023-02-14 timestamp for firebase
2023-02-17 dev return to basic
2023-03-04 Firebase ready
    stream & update
2023-03-12 cruz firebase and events
2023-06-07 etregado, error en calendario
2023-06-14 separate
    Not working, externt variables not same as
2023-06-14 one file
2023-06-20 separate ok
    ok separate
2023-06-28 pruebas du subida de firebase
    sube el archivo pero no lo puede poner en en objeto
2023-06-28 Firebase
    upload and dowload alsmot ready
2023-06-30 firebase
    REady, accept all msg
2023-06-30 firebase and unixtime
    Ready to save and update info
2023-07-01 lora separete
2023-07-03 loraseparate
    compatibility test
2023-07-03 Auto stash before merge of "dev_sep" and "origin/dev_sep"
2023-07-04 spiffs
    empty
2023-07-04 lora send
    RMRadio ok send akc
2023-07-05 Lora
    ack ready TX+RX
2023-07-06 reset button fail
2023-07-06 lora-receiver ok
    Events reset and previous day not ready
2023-07-07 unixtime adjust
    reset events not ready, restart not ready
2023-07-08 Version 1 cruz ready
    ready
2023-07-08 revision de color
    El color falla al cambio
2023-07-09 color en test
2023-07-11 kary
2023-07-12 bt boton listo
2023-07-13 fast update firebase
    falta hacer merge correcto en events
2023-07-15 fast update ready
    Events, Color, Days fast update
2023-07-15 fast update and firmware
2023-07-16 more file size to spiffs, events
2023-07-16 testing neo clock
    rtf hardware fail
2023-07-17 download es correcto
    se muestra la hum y temp durante 10 seg
2023-07-17 Fotos App
2023-07-17 firebase OTA check
2023-07-17 OTA Cruz check
    Version adn OTA cruz ready
2023-07-19 registered not change color ok
    Problem whith registered answer
2023-07-19 change seconsds for millis
2023-08-10 dias separate
2023-08-10 r7 prev
2023-08-11 Read clock ready
    Prevent halted whit delay
2023-08-11 manual app and neoclock_lite test
2023-09-06 neoclock wifi manager
2023-09-07 Firebase array json obj
    Insert text on events for prevent array auto convertion
2024-02-06 wip demo sensors
2024-02-08 wip, not ready
2024-02-15 OLED ready, db almost
2024-02-16 db update ok
2024-02-16 sensor box ready
2024-02-16 sensor box and lora OK
2024-02-16 preparando para wifi new
2024-02-16 wip working
2024-02-26 spiff size 2048
    Espacio no sufuciente, wip
2024-02-26 wip almost
2024-02-28 firebase fast update wip
2024-02-28 Ready fast change
2024-03-19 binario
